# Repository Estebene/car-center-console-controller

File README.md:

# Center Console Controller For Fiat Brava

## Project Overview
My friend has a Fiat Brava and has been working to [replace the center console with a giant Tesla style screen](https://www.reddit.com/r/raspberry_pi/comments/1ilmfnt/car_infotainment_system/). He asked me to help create all of the electronics for this ~~silly~~ revolutionary project. The goal was to design a system so that all of the controls that were previously accessible through the mostly mechanical center console could now be accessed through the screen. Being a software engineer my friend had already developed a system to do this. 

It involved using a Raspberry Pi running Android OS for the GUI displayed on the screen which connected to another Raspberry Pi running a Debian Linux based OS over websockets. The second Raspberry Pi would control the Car's systems through its GPIO. It was necessary because Android OS does not support the GPIO on the Raspberry Pi. Android OS was required on the first Raspberry Pi as it offered the best touchscreen and USB GPS support.

## Initial Prototyping
I thought the electrical design would be best implemented as a PCB with various components. However, before a schematic and PCB is developed it is often wise to do some initial prototyping to figure out the requirements and specifications for the design. Cheap Aliexpress boards such as the IBT-2 and an 8 channel relay board and a Raspberry Pi 4 were used to test all of the functionality of the car. We referred to the car's electrical wiring diagrams available in the manual. ChatGPT was used to develop much of the code as this allowed for rapid prototyping.

A difficult problem we ran into was that when controlling the fan through PWM it made audible noises. At low PWM frequencies the fan would make a variable whoosing sound and at higher frequencies (~1000Hz) a whining sound could be heard. The previous fan controller used selectable position resistor ladder to determine the power to the fan and thus the speed so I became worried that the motor was not suitable for controlling with PWM. We tried placing a capacitor across the fan to smooth out the switched voltage but this did not help. To help diagnose the problem I used an oscilloscope to measure the voltage across the fan, this showed than even though the PWM frequency might be set at 50kHz in software only 1kHz might be generated on the output of the Raspberry Pi. This is because the PWM was implemented in software using function calls to turn the GPIO on and off quickly. Eventually, we found that the PWM frequency can be increased significantly by using the Raspberry Pi's built-in hardware PWM. Implementing this fixed the issue and the fan no longer made unexpected noises.

## Electrical Design

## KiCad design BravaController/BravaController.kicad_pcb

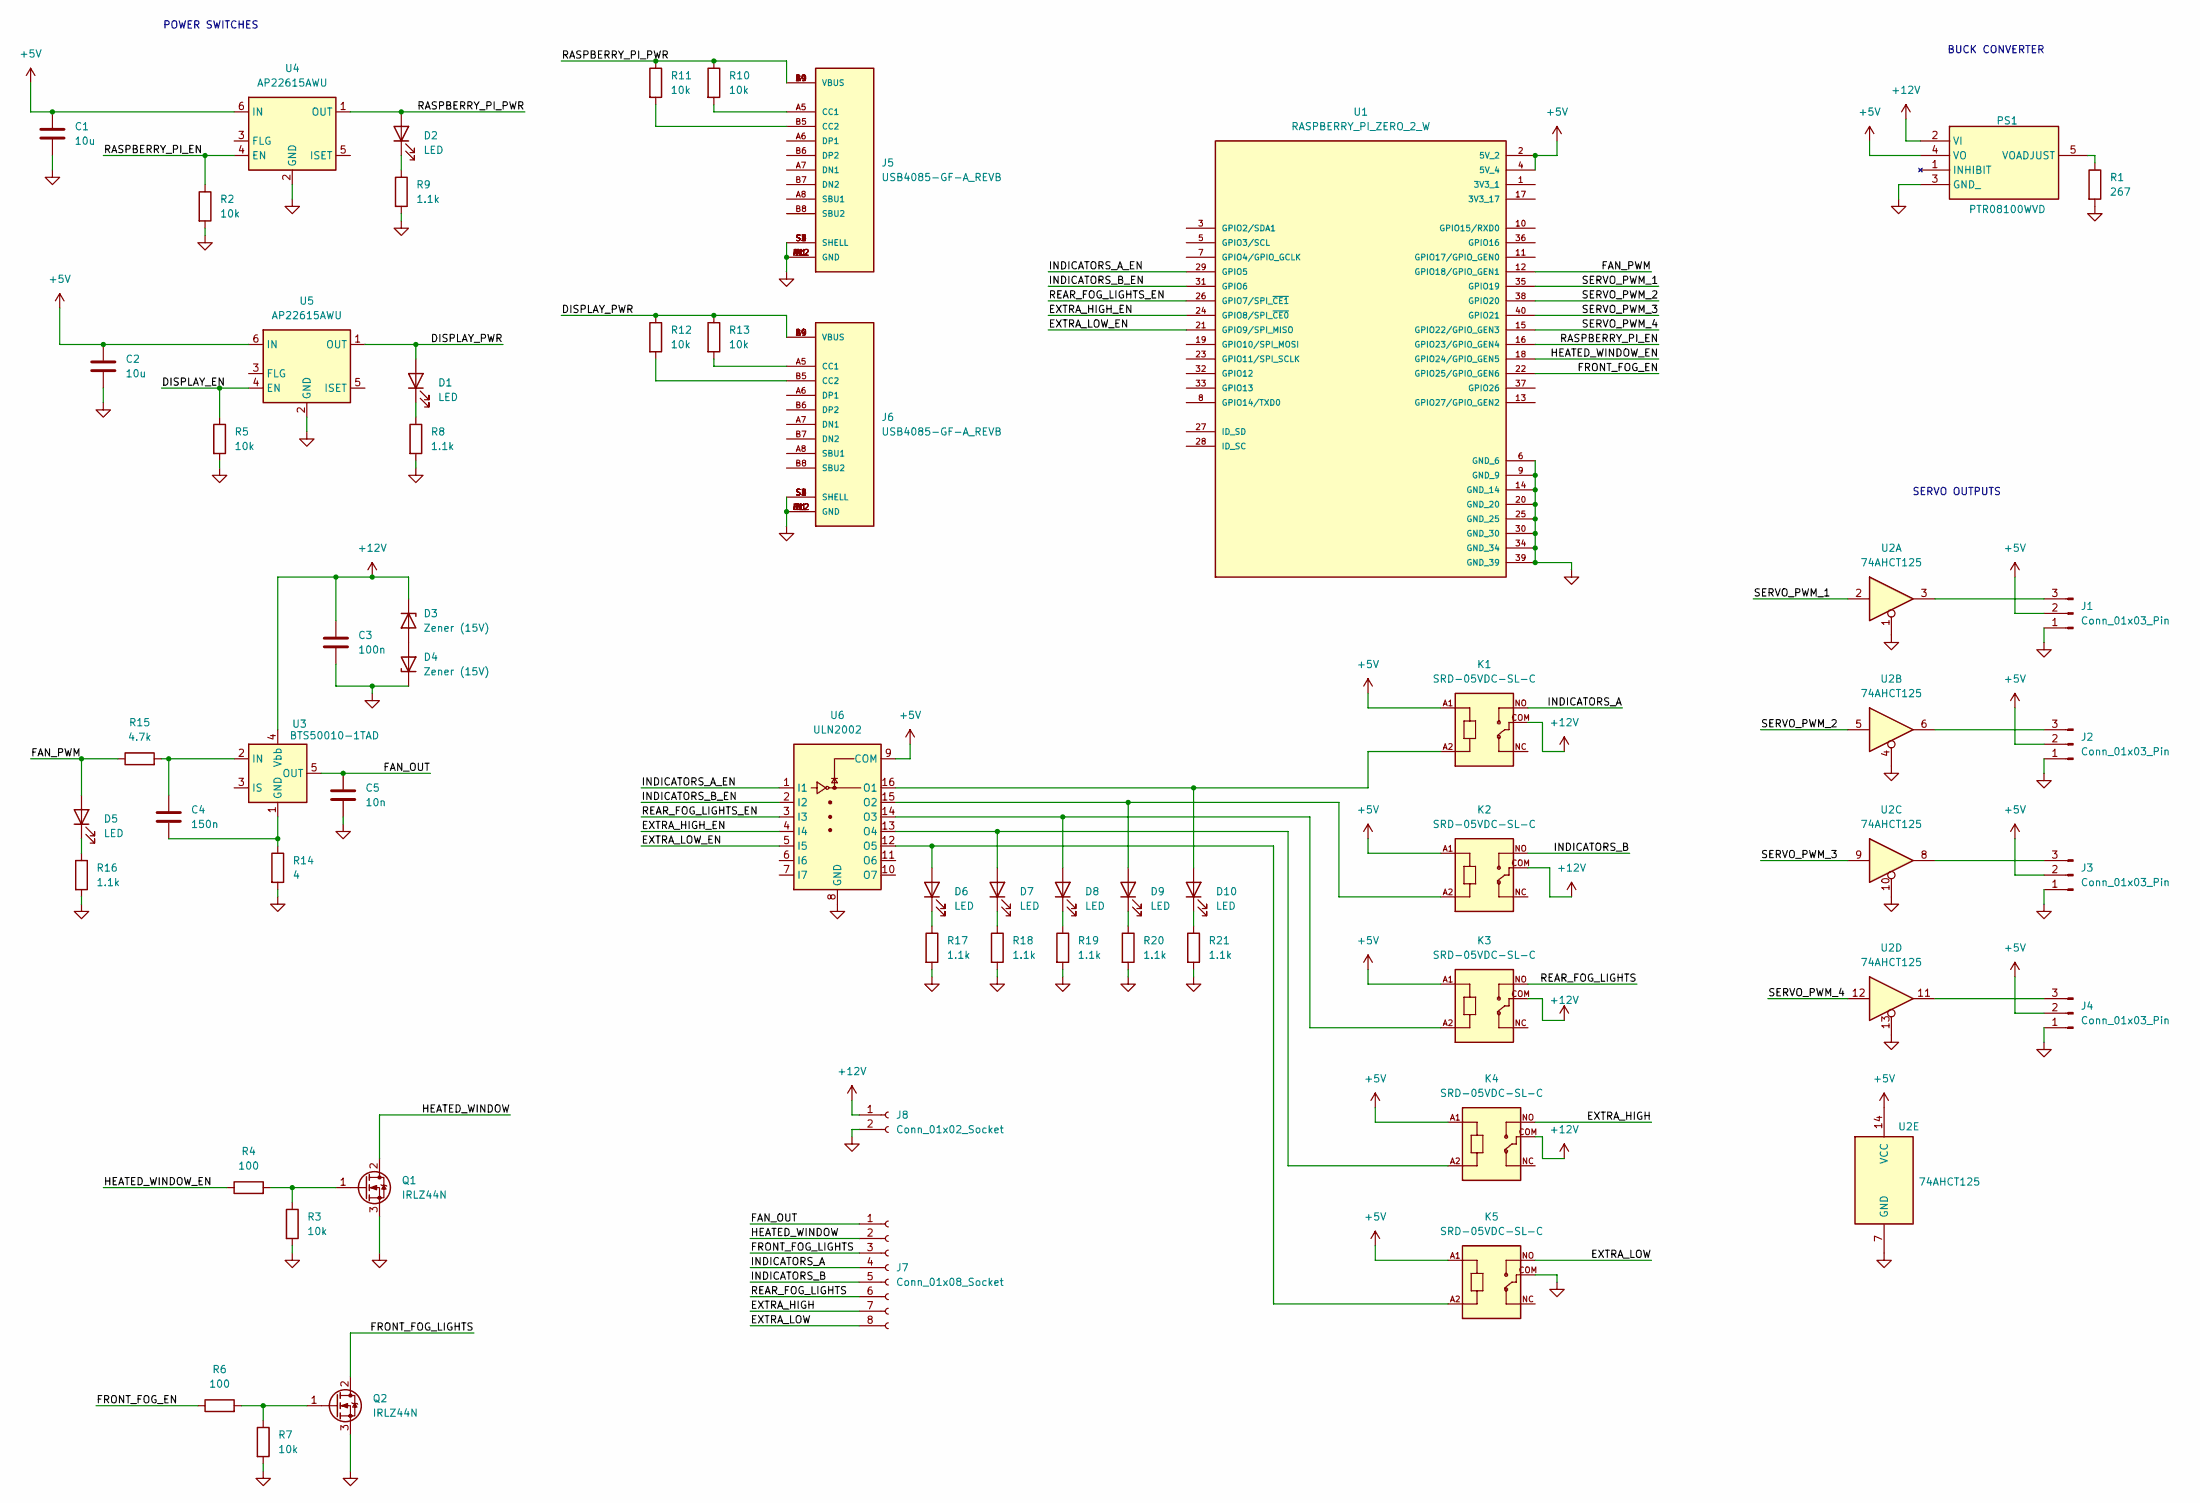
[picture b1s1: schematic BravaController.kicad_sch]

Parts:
C1, C2: 10u; C_0805_2012Metric_Pad1.18x1.45mm_HandSolder
C3: 100n; C_0805_2012Metric_Pad1.18x1.45mm_HandSolder
C4: 150n; C_0805_2012Metric_Pad1.18x1.45mm_HandSolder
C5: 10n; C_0805_2012Metric_Pad1.18x1.45mm_HandSolder
D1, D2, D5, D6, D7, D8, D9, D10: LED; LED_0805_2012Metric_Pad1.15x1.40mm_HandSolder
D3, D4: Zener (15V); SOT-23
J1, J2, J3, J4: Conn_01x03_Pin; PinHeader_1x03_P2.54mm_Vertical
J5, J6: USB4085-GF-A_REVB; GCT_USB4085-GF-A_REVB; PARTREV B
J7: Conn_01x08_Socket; Molex_KK-396_5273-08A_1x08_P3.96mm_Vertical
J8: Conn_01x02_Socket; AMASS_XT60PW-M_1x02_P7.20mm_Horizontal
K1, K2, K3, K4, K5: SRD-05VDC-SL-C; RELAY_SRD-05VDC-SL-C
PS1: PTR08100WVD; Mouser Part Number 595-PTR08100WVD
Q1, Q2: IRLZ44N; TO-220-3_Vertical
R1: 267; R_0805_2012Metric_Pad1.20x1.40mm_HandSolder
R2, R3, R5, R7, R10, R11, R12, R13: 10k; R_0805_2012Metric_Pad1.20x1.40mm_HandSolder
R4, R6: 100; R_0805_2012Metric_Pad1.20x1.40mm_HandSolder
R8, R9, R16, R17, R18, R19, R20, R21: 1.1k; R_0805_2012Metric_Pad1.20x1.40mm_HandSolder
R14: 4; R_0805_2012Metric_Pad1.20x1.40mm_HandSolder
R15: 4.7k; R_0805_2012Metric_Pad1.20x1.40mm_HandSolder
U1: RASPBERRY_PI_ZERO_2_W; MODULE_RASPBERRY_PI_ZERO_2_W; PARTREV April 2024
U2: 74AHCT125; SOIC-14_3.9x8.7mm_P1.27mm
U3: BTS50010-1TAD; TO-263-7_TabPin4
U4, U5: AP22615AWU; SOT-23-6
U6: ULN2002; SOIC-16_3.9x9.9mm_P1.27mm

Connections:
+5V: C1.1, C2.1, J1.2, J2.2, J3.2, J4.2, K1.A1, K2.A1, K3.A1, K4.A1, K5.A1, PS1.4 (VO), U1.2 (5V_2), U1.4 (5V_4), U2.14 (VCC), U4.6 (IN), U5.6 (IN), U6.9 (COM)
+12V: C3.1, D3.1 (K), J8.1, K1.COM, K2.COM, K3.COM, K4.COM, PS1.2 (VI), U3.4 (Vbb)
/DISPLAY_EN: R5.1, U5.4 (EN)
/DISPLAY_PWR: D1.2 (A), J6.A4 (VBUS), J6.A9 (VBUS), J6.B4 (VBUS), J6.B9 (VBUS), R12.1, R13.1, U5.1 (OUT)
/EXTRA_HIGH: J7.7, K4.NO
/EXTRA_HIGH_EN: U1.24 (GPIO8/SPI_~CE0), U6.4 (I4)
/EXTRA_LOW: J7.8, K5.NO
/EXTRA_LOW_EN: U1.21 (GPIO9/SPI_MISO), U6.5 (I5)
/FAN_OUT: C5.1, J7.1, U3.5 (OUT), U3.6 (OUT), U3.7 (OUT)
/FAN_PWM: D5.2 (A), R15.1, U1.12 (GPIO18/GPIO_GEN1)
/FRONT_FOG_EN: R6.1, U1.22 (GPIO25/GPIO_GEN6)
/FRONT_FOG_LIGHTS: J7.3, Q2.2 (D)
/HEATED_WINDOW: J7.2, Q1.2 (D)
/HEATED_WINDOW_EN: R4.1, U1.18 (GPIO24/GPIO_GEN5)
/INDICATORS_A: J7.4, K1.NO
/INDICATORS_A_EN: U1.29 (GPIO5), U6.1 (I1)
/INDICATORS_B: J7.5, K2.NO
/INDICATORS_B_EN: U1.31 (GPIO6), U6.2 (I2)
/RASPBERRY_PI_EN: R2.1, U1.16 (GPIO23/GPIO_GEN4), U4.4 (EN)
/RASPBERRY_PI_PWR: D2.2 (A), J5.A4 (VBUS), J5.A9 (VBUS), J5.B4 (VBUS), J5.B9 (VBUS), R10.1, R11.1, U4.1 (OUT)
/REAR_FOG_LIGHTS: J7.6, K3.NO
/REAR_FOG_LIGHTS_EN: U1.26 (GPIO7/SPI_~CE1), U6.3 (I3)
/SERVO_PWM_1: U1.35 (GPIO19), U2.2
/SERVO_PWM_2: U1.38 (GPIO20), U2.5
/SERVO_PWM_3: U1.40 (GPIO21), U2.9
/SERVO_PWM_4: U1.15 (GPIO22/GPIO_GEN3), U2.12
GND: C1.2, C2.2, C3.2, C5.2, D4.1 (K), J1.1, J2.1, J3.1, J4.1, J5.A1 (GND), J5.A12 (GND), J5.B1 (GND), J5.B12 (GND), J5.S1 (SHELL), J5.S2 (SHELL), J5.S3 (SHELL), J5.S4 (SHELL), J6.A1 (GND), J6.A12 (GND), J6.B1 (GND), J6.B12 (GND), J6.S1 (SHELL), J6.S2 (SHELL), J6.S3 (SHELL), J6.S4 (SHELL), J8.2, K5.COM, PS1.3 (GND_), Q1.3 (S), Q2.3 (S), R1.2, R2.2, R3.2, R5.2, R7.2, R8.2, R9.2, R14.2, R16.2, R17.2, R18.2, R19.2, R20.2, R21.2, U1.6 (GND_6), U1.9 (GND_9), U1.14 (GND_14), U1.20 (GND_20), U1.25 (GND_25), U1.30 (GND_30), U1.34 (GND_34), U1.39 (GND_39), U2.1, U2.4, U2.7 (GND), U2.10, U2.13, U4.2 (GND), U5.2 (GND), U6.8 (GND)
unnamed: D1.1 (K), R8.1
unnamed: D2.1 (K), R9.1
unnamed: D3.2 (A), D4.2 (A)
unnamed: D5.1 (K), R16.1
unnamed: D6.2 (A), K5.A2, U6.12 (O5)
unnamed: D6.1 (K), R17.1
unnamed: D7.2 (A), K4.A2, U6.13 (O4)
unnamed: D7.1 (K), R18.1
unnamed: D8.2 (A), K3.A2, U6.14 (O3)
unnamed: D8.1 (K), R19.1
unnamed: D9.2 (A), K2.A2, U6.15 (O2)
unnamed: D9.1 (K), R20.1
unnamed: D10.2 (A), K1.A2, U6.16 (O1)
unnamed: D10.1 (K), R21.1
unnamed: J1.3, U2.3
unnamed: J2.3, U2.6
unnamed: J3.3, U2.8
unnamed: J4.3, U2.11
unnamed: J5.A5 (CC1), R10.2
unnamed: J5.B5 (CC2), R11.2
unnamed: J6.A5 (CC1), R13.2
unnamed: J6.B5 (CC2), R12.2
unnamed: PS1.5 (VOADJUST), R1.1
unnamed: Q1.1 (G), R3.1, R4.2
unnamed: Q2.1 (G), R6.2, R7.1
unnamed: C4.2, R14.1, U3.1 (GND)
unnamed: C4.1, R15.2, U3.2 (IN)

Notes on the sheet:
BUCK CONVERTER
SERVO OUTPUTS
POWER SWITCHES

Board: 4 copper layers, 58 parts (0 on the bottom side), 54 nets, no tracks yet.

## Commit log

2025-07-08 Added .gitignore
2025-07-10 Developed Draft Schematic for Design
2025-07-10 Updated README.md to include more detail on initial prototyping phase
2025-07-10 Draft PCB arrangement
